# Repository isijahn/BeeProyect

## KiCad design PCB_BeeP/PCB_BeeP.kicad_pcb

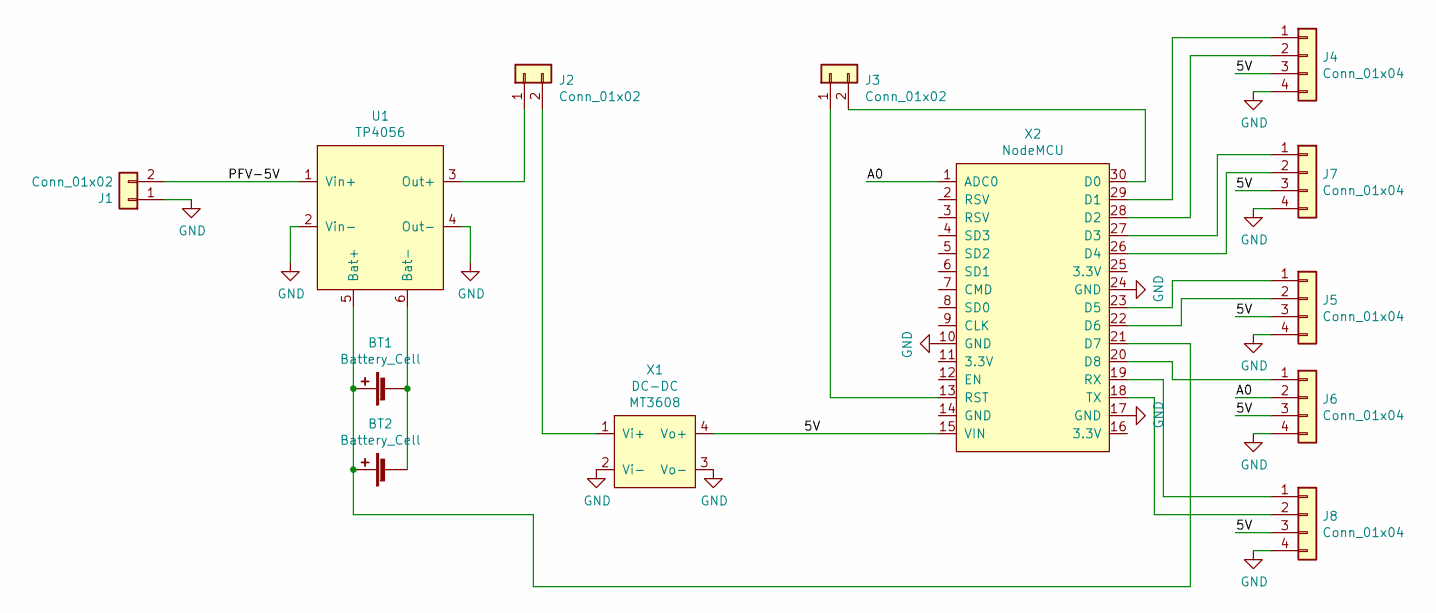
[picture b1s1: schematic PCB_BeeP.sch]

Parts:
BT1, BT2: Battery_Cell; BatteryHolder_Keystone_1042_1x18650
J1: Conn_01x02; Tb-2x1-5p-TH-V
J2: Conn_01x02; JST_EH_B2B-EH-A_1x02_P2.50mm_Vertical
J3: Conn_01x02; PinHeader_1x02_P2.54mm_Vertical
J4, J5, J6, J7, J8: Conn_01x04; JST_EH_B4B-EH-A_1x04_P2.50mm_Vertical
U1: TP4056
X1: DC-DC; MT3608
X2: NodeMCU; ESP8266_lolin

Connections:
/5V: J4.3, J5.3, J6.3, J7.3, J8.3, X1.4 (Vo+), X2.15 (VIN)
/A0: J6.2, X2.1 (ADC0)
/PFV-5V: J1.2, U1.1 (Vin+)
GND: J1.1, J4.4, J5.4, J6.4, J7.4, J8.4, U1.2 (Vin-), U1.4 (Out-), X1.2 (Vi-), X1.3 (Vo-), X2.10 (GND), X2.17 (GND), X2.24 (GND)
unnamed: BT1.1 (+), BT2.1 (+), U1.5 (Bat+), X2.21 (D7)
unnamed: BT1.2 (-), BT2.2 (-), U1.6 (Bat-)
unnamed: J2.1, U1.3 (Out+)
unnamed: J2.2, X1.1 (Vi+)
unnamed: J3.1, X2.13 (RST)
unnamed: J3.2, X2.30 (D0)
unnamed: J4.1, X2.29 (D1)
unnamed: J4.2, X2.28 (D2)
unnamed: J5.1, X2.23 (D5)
unnamed: J5.2, X2.22 (D6)
unnamed: J6.1, X2.20 (D8)
unnamed: J7.1, X2.27 (D3)
unnamed: J7.2, X2.26 (D4)
unnamed: J8.1, X2.19 (RX)
unnamed: J8.2, X2.18 (TX)

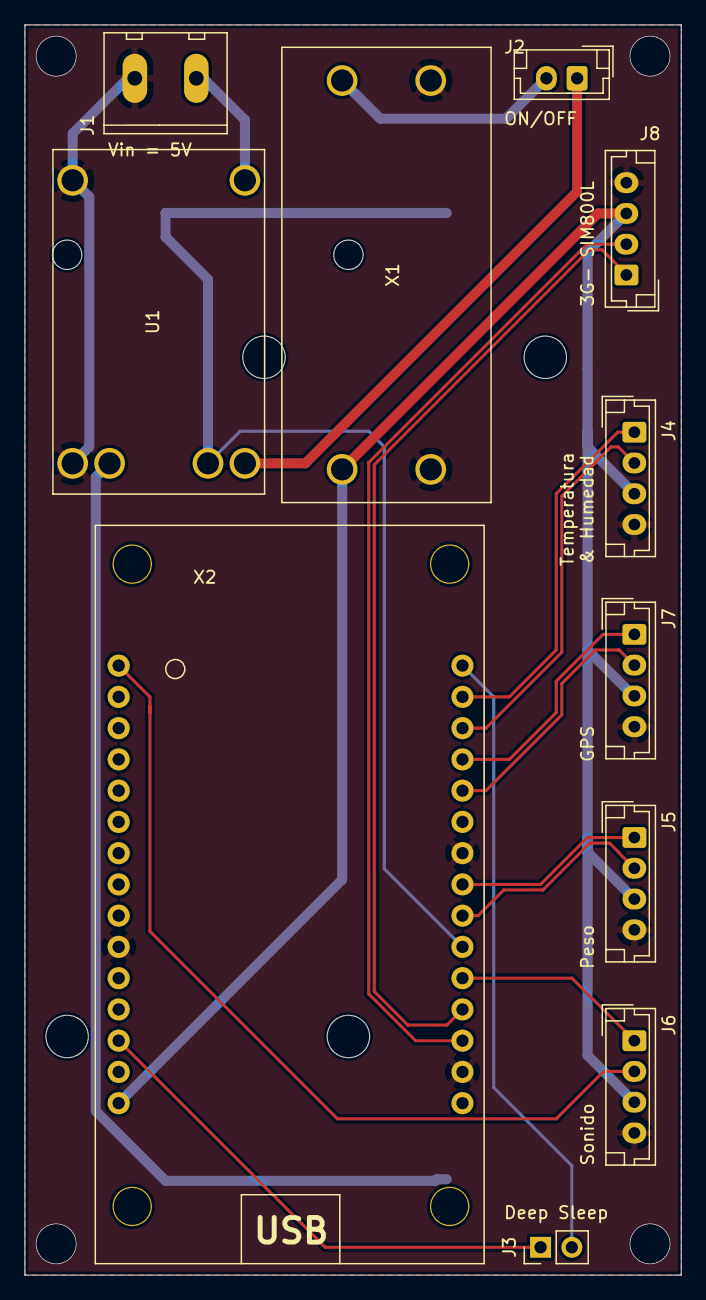
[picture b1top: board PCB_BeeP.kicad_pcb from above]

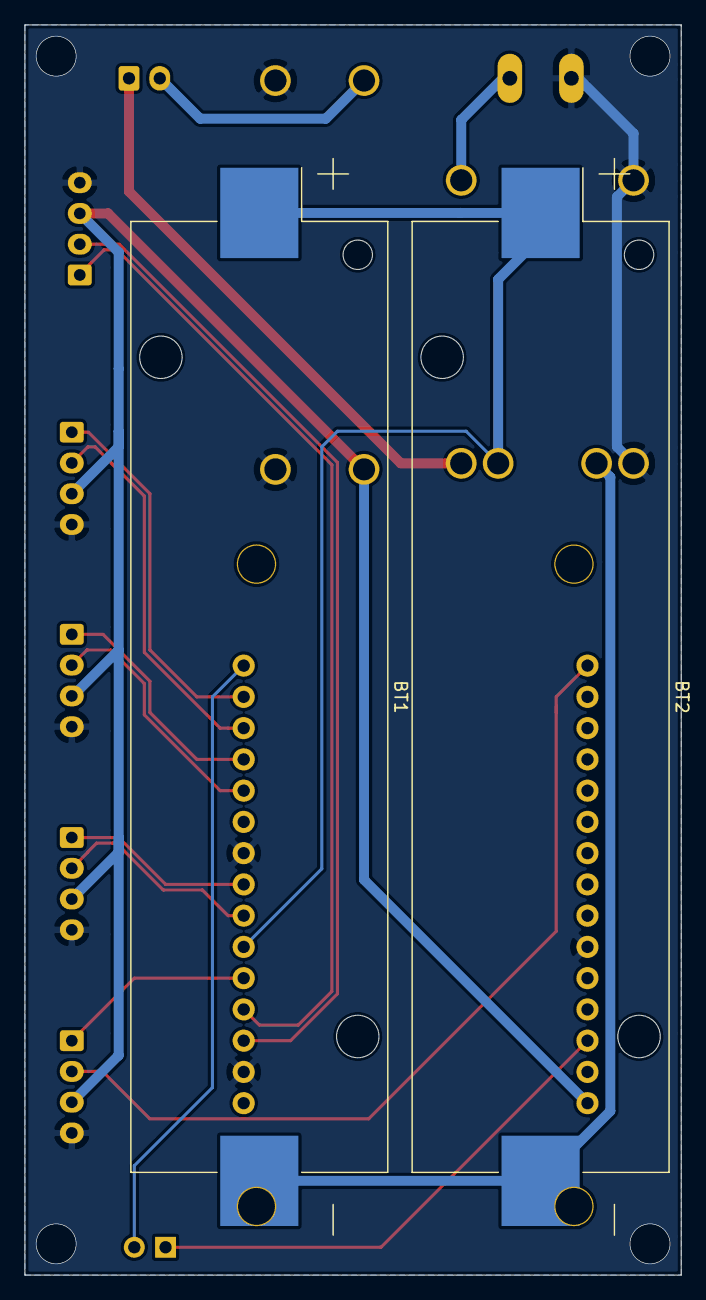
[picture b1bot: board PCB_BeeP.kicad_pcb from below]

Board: 2 copper layers, 53.3 x 101.6 mm, 13 parts (2 on the bottom side), 19 nets.

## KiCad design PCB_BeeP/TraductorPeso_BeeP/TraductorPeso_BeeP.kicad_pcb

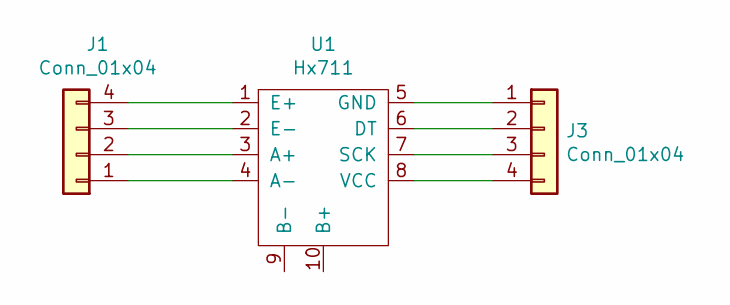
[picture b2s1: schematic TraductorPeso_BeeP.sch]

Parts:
J1, J3: Conn_01x04; JST_EH_S4B-EH_1x04_P2.50mm_Horizontal
U1: Hx711

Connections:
unnamed: J1.1, U1.4 (A-)
unnamed: J1.2, U1.3 (A+)
unnamed: J1.3, U1.2 (E-)
unnamed: J1.4, U1.1 (E+)
unnamed: J3.1, U1.5 (GND)
unnamed: J3.2, U1.6 (DT)
unnamed: J3.3, U1.7 (SCK)
unnamed: J3.4, U1.8 (VCC)

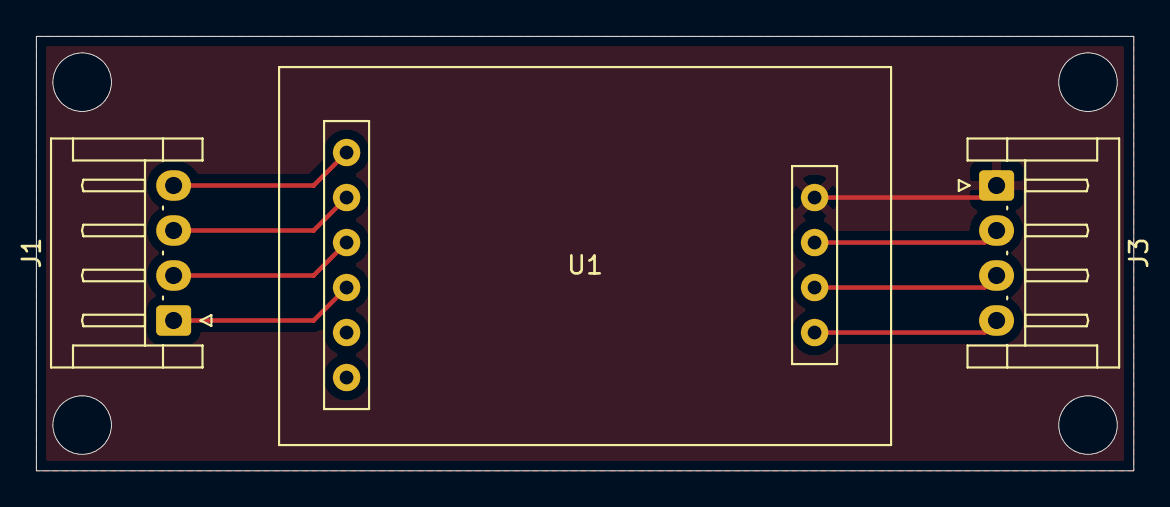
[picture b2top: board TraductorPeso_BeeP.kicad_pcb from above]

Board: 2 copper layers, 61.0 x 24.1 mm, 3 parts (0 on the bottom side), 8 nets.

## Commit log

2021-02-15 Commit message
2021-08-10 Prototipo 2
    Versión con PCB de módulos
2021-08-11 PCB abejas V3
    Agregué la PCB traductora de peso que iría en la plataforma a agregar
2021-08-22 Placa abejas final - Isi
    Agregados conectores porsiaca (GPS y 3G), pin de monitoreo de carga de la batería y modificación al lado de potencia (se asume que se tendrá para entonces un regulador MPPT para el panel FV, modifica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
2021-08-22 Modulo hx711
